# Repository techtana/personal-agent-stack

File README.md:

# personal-agent-stack

**Direction (2026-10-26): private first.** Every request is to be processed by private models, on owned hardware
or confidential cloud VMs; external model APIs become an optional, explicit, gated user choice. The plans are in
[docs/plans/](docs/plans/README.md). Since 2026-10-26 the build routes every tier to local models, with or without an
API key; external models stay off until the privacy gate exists.

A local-first coding-agent stack for one developer on one GPU workstation, composed from open-source
tools rather than a custom harness. Six department agents (app-dev, testing, security, devops,
code-review, docs) are defined once and generated into Claude Code, OpenCode, Open WebUI and a LiteLLM
gateway that routes each request to the cheapest tier that can do the job: a small always-resident
model for autocomplete, a mixture-of-experts coder on the local GPU for routine work, and Claude
Haiku/Sonnet/Opus 5.5 through the gateway only when complexity, context size or a stall demands it.

```
 Claude Code (terminal / VS Code / desktop)   OpenCode   Open WebUI (chat, thumbs)   promptfoo (evals)
            │ Anthropic /v1/messages              │ OpenAI /v1       │                     │
            └──────────────┬──────────────────────┴──────────────────┴─────────────────────┘
                           ▼
            LiteLLM gateway :4000  (one model alias per department = complexity router)
              local-fim · local-small · local-primary   (private only; external models off: policy/privacy.yaml)
              JSONL traces → traces/litellm/     OTLP → Phoenix :6006
                 │                                              │
      Ollama (native, GPU) :11434
      qwen2.5-coder:1.5b-base · qwen3.5:9b · qwen3.6:35b-a3b-coding (MoE, experts in RAM)

 Orchestrator MCP :8765  delegate/get_job/record_lesson   ·   hooks → traces/claude/   ·   nightly retro → PR
```

Design, decisions and measurements: [docs/ORCHESTRATOR-DESIGN.md](docs/ORCHESTRATOR-DESIGN.md).
Private-first multi-user plans (cloud-led on confidential VMs, local-led), privacy gate and installation:
[docs/plans/](docs/plans/README.md).
Stable rules for agents: [AGENTS.md](AGENTS.md). State and lessons: [memory/](memory/).
Manuals: [installation](docs/manuals/installation.md) · [choosing drives](docs/manuals/choosing-drives.md) ·
[user guide](docs/manuals/user-guide.md) · [troubleshooting](docs/manuals/troubleshooting.md).

**When to use it:** you write code with AI agents on your own GPU workstation, and you want routine work to stay
local, private and free. External models are off; they will only ever be an explicit, gated choice (docs/plans/).
It is not a team or hosted service yet.

## Prerequisites

| Tool | Version | Notes |
|---|---|---|
| NVIDIA GPU | 12 GB VRAM for the default lineup; 8 GB works with the `small-gpu` class | 32 GB system RAM enables the MoE primary; 16 GB falls back to a dense 9B |
| [uv](https://docs.astral.sh/uv/) | 0.12+ | the only hard requirement; it fetches Python 3.11/3.12 and the tools |
| [Ollama](https://ollama.com/download) | 0.40+ | native install (Windows: `winget install --id Ollama.Ollama`); not in Docker |
| Claude Code | 2.1.293+ | `winget install --id Anthropic.ClaudeCode` or the VS Code extension / desktop app |
| Node | 24+ | only for `npx promptfoo` evals |

Docker is optional (`infrastructure/docker-compose.yml`); the reference machine runs everything natively.

## Quick start

```powershell
# Windows: double-click install.cmd (or run .\scripts\setup.ps1). It installs the app into its own folder
# (%LOCALAPPDATA%\Programs\AgentStack; its logs, settings and data stay there, not in this repository). Then a
# window asks which features to install (each row shows its disk, GPU, CPU and RAM load on this PC; the local
# models and the gateway are required) and where the models and the Python tools go, and setup runs in the
# background: .env secrets, Ollama env, uv tools, configs, model downloads. Run install.cmd again after a pull
# to update the app, or Install / Remove on the tray's Features card to add or remove features.
uv run scripts/stack.py up   # start phoenix, litellm, orchestrator, open_webui
uv run scripts/stack.py smoke
```

```bash
# Linux / macOS / WSL / Git Bash
./scripts/setup.sh && uv run scripts/stack.py up && uv run scripts/stack.py smoke
```

To keep the stack running in the background, use the tray app instead of `up`:

```
uv run scripts/stack.py tray                    # starts the services and a tray icon (Windows: under the ^ hidden icons)
uv run scripts/stack.py tray --install-startup  # optional: start the tray at login
```

Clicking the icon opens a status window with three tabs (since 2026-10-27): **Overview** (services, start/stop, models
loaded in Ollama), **Usage** (requests, tokens, latency, tok/s and cost per model, from `traces/litellm/`) and
**Settings** (models, context sizes, tracing, Open WebUI, Ollama runtime; **Apply** saves to `machines/<HOST>.yaml`,
rebuilds and restarts what changed) and **Resources** (live CPU, RAM,
driver-reported GPU engine use and dedicated GPU memory per process; unavailable readings show as `-`). The icon is green when everything is up, amber when something is down, red when
the gateway or Ollama is down. The tray runs outside any terminal or Claude Code session, so its services keep running.
"Quit (keep services running)" closes only the tray; "Stop services and quit" stops everything.

After a quit, start it again from the Start menu entry **Agent Stack** (the installer creates it) or by double-clicking
`start.cmd` in the repository folder; either opens the window when the tray is already running. `stop.cmd` closes the
tray and stops its services (Ollama keeps running), even when the tray has already been quit.

For services that must run before anyone signs in (edge mode), register one Task Scheduler task per service instead,
from an elevated terminal: `uv run scripts/stack.py tasks install`. See the
[installation manual](docs/manuals/installation.md#run-the-services-before-sign-in-optional).

Then:

- **Claude Code on your subscription (default):** open this repo in Claude Code. The departments appear as
  subagents (`@security review src/auth.py`), `/retro`, `/harden`, `/brainstorm`, `/why-routed` as skills,
  `/ux-rules` for UX reviews against a researched rule catalog, `/claude-security-audit` for a privacy and safety
  check of your Claude setup, and the orchestrator as an MCP server (approve it once). Heavy work stays on your plan.
- **Claude Code on the local gateway:** `.\scripts\claude-local.ps1` (or `.sh`). A separate config dir
  (`~/.claude-local`) points at LiteLLM, so local models serve `sonnet`/`haiku` aliases and plan quota is untouched.
- **Open WebUI:** http://127.0.0.1:3000 -> create the admin user -> Workspace -> Models -> Import each
  `config/openwebui/<dept>.json`; Admin -> Integrations -> External Tool Servers -> MCP (Streamable HTTP)
  `http://127.0.0.1:8765/mcp` with `ORCHESTRATOR_BEARER` from `.env` as the bearer (not `WEBUI_SECRET_KEY`) and
  ID `personal-agent-stack`; the department models switch its tools on in new chats.
- **OpenCode:** `opencode.json` registers the gateway as provider `litellm`; agents are in `.opencode/agents/`.
- **Autocomplete in VS Code:** `config/continue/config.yaml` (Continue, autocomplete role only).

## Configuration

| Where | What |
|---|---|
| `machines/_defaults.yaml` | hardware classes -> model lineup, Ollama env, ports, service modes |
| `machines/<HOST>.yaml` | detected hardware + your overrides (`models.primary`, `model_store`); written by the installer, local to this computer, never committed |
| `policy/privacy.yaml` | private-first policy: deployment location, `external.enabled` (off; the build refuses `true` until the privacy gate exists) |
| `agents/<id>.yaml` | one department: prompt, tools, Claude Code model alias, routing tiers, evals |
| `agents/_common.md` | working agreements appended to every department prompt |
| `.env` | `LITELLM_MASTER_KEY`, `ORCHESTRATOR_BEARER`, `WEBUI_SECRET_KEY`, Claude Code's own `LITELLM_CLAUDE_KEY` and `ORCHESTRATOR_CLAUDE_BEARER`, `ANTHROPIC_API_KEY` (unused until external models exist) |
| `.claude/settings.json` | hooks (trace capture), permissions, gateway hint headers |
| `.claude/settings.local.json` | per-machine: Claude Code's own keys (never the stack's), `autoMemoryDirectory` -> `memory/claude/` |

After any change: `uv run scripts/stack.py build` (and `up`/`down` to restart the gateway).

## Cost model

- Autocomplete, embeddings, titles/summaries and the simple/medium tiers are local: $0.
- Every tier is local, with or without an API key in `.env` (private first, since 2026-10-26). External models will be
  explicit aliases behind the privacy gate, never a tier or fallback (docs/plans/SHARED-COMPONENTS.md section 2).
- Interactive Claude Code on the subscription costs no API dollars; a credential variable (profile B or
  an API key in the gateway) bills per token. Traces record cost per request; `retro` reports cost per department.

## Commands

```
uv run scripts/stack.py doctor [--write-profile [--refresh]]   hardware, tools, ports, chosen class
uv run scripts/stack.py check [--no-drives] [--json]          this PC, and which models and features are recommended on it
uv run scripts/stack.py profile | build | setup | pull [--all]
uv run scripts/stack.py up [svc...] | down [svc...] | status
uv run scripts/stack.py tray [--show | --foreground | --status | --stop | --install-startup | --remove-startup]
uv run scripts/stack.py tasks install|remove|start|stop|status|xml [svc...] [--trigger startup|logon]
uv run scripts/stack.py bench [--model m] [--num-ctx n] [--tokens n] [--runs n]
uv run scripts/stack.py smoke [--dept id] [--skip-mcp] [--media | --media-only]
uv run scripts/stack.py media check|install|provision          ComfyUI and image models under media.root (path guard first)
uv run scripts/stack.py media gpu chat|media                   hand the GPU to chat (free ComfyUI) or media (unload Ollama)
uv run scripts/stack.py dictate install|start|stop|status|check voice typing in any app: Ctrl+Alt+D or the mic button; Ctrl+Alt+R or the pencil button refines selected text
uv run scripts/stack.py dictate transcribe note.wav [--style concise] [--model m]   the voice typing pipeline on a recording
uv run scripts/stack.py why-routed [--last n] [--days n]
uv run scripts/stack.py retro -- --days 7 [--reflect local-small|none] [--pr]
uv run scripts/stack.py skills-sync [--dry-run]                 copy your own skills into skills/ (rules: skills/sync.yaml)
npx promptfoo@0.125.0 eval -c evals/<dept>/promptfooconfig.yaml --repeat 3
```

## Troubleshooting

See [docs/manuals/troubleshooting.md](docs/manuals/troubleshooting.md): health checks, log locations and a
symptom → cause → fix table. Logs are in `.run/logs/<service>.log`; Ollama's is `%LOCALAPPDATA%\Ollama\server.log`.

## Assumptions and limitations

- It is built for one developer on one workstation. Every service listens on 127.0.0.1 only, and nothing is multi-user.
- It needs an NVIDIA GPU with at least 8 GB of VRAM. On 32 GB of RAM, the 35B MoE decodes at about 25 tok/s,
  against about 52 for the dense 9B (the reference machine, 2026-10-25).
- Only Windows is verified (2026-10-26). Service management on Linux and macOS is written but untested, and so is the Docker compose path.
- Cloud tiers have not been exercised yet, because no API key is on the reference machine. Claude Code profile B has
  not been run as a live session yet. Since 2026-10-28 the build is private only, so no tier can reach an external
  model at all (`policy/privacy.yaml`, `external.enabled: false`).
- AI agents on the machine run as the owner's own account, so nothing at the operating-system level stops them reading
  personal files. A plan to fix that exists ([AGENT-FILE-ISOLATION.md](docs/plans/AGENT-FILE-ISOLATION.md)); nothing
  is applied yet.
- Routing budgets and LiteLLM's adaptive router need Postgres, so they are not in use.

## Known issues

Tracker: this repository's GitHub issues.

- Phoenix does not start on the reference machine since 2026-10-26: Smart App Control blocks compiled modules in its tool
  environment (pyarrow, sqlalchemy, pandas). The plans remove Phoenix; until then turn **Phoenix tracing** off in the
  tray's Settings tab. The tray's Usage tab reads the JSONL traces and does not need Phoenix.
- Smart App Control may also start blocking the uv tool environments' `python.exe` (see the open items in `memory/state.md`).
- The LiteLLM admin UI (`/ui`, the tray's **Open gateway admin** link) shows "Not connected to DB!" because it needs Postgres.
- Images (2026-11-04): Smart App Control refused PyAV 19.0.2 and 16.0.1 inside ComfyUI's environment; 17.0.0 runs,
  so setup pins `av==17.0.0` (`media.SAC_PINS`). A future refusal shows as "An Application Control policy has blocked
  this file" in `.run/logs/comfyui.log`.
- Vision, speech, the Auto router, style transfer, video with audio, music and web search from the multimodal plan
  are not built yet (docs/design/plans/2026-11-01-multimodal-stack.md).
- `local-reviewer` points at `flint:40b-a2b`, which is not pulled. No tier routes to it.
- A chat message cannot switch models. Open WebUI sends each message to the model picked in the chat's model list
  (or with `@` in the input box), and `local-primary` is always the local model.
- `/ux-rules` lives in `.claude/skills/ux-rules/`, not in the `skills/` library. The commit that moves it (`a8400c9`)
  landed on the PR branch after PR #13 merged (2026-11-01).
- D: on the reference machine is exFAT, which has no file permissions, so any account can read everything on it (found
  2026-10-30). Personal data there must move, or the drive must be reformatted to NTFS, before the agent account split
  can protect it.
- From 2026-10-26 (`d93211b`) to 2026-11-07 a stray Open WebUI database (`litellm.db`, `-shm`, `-wal`) was committed at
  the repository root. Its user and chat tables were empty, but its settings held the gateway's `LITELLM_MASTER_KEY`,
  and it is still in the public history. Rotate that key.
- Until 2026-11-07 the machine profile, docs and three commits' author field named the owner's computer, Windows
  account or email address. The current files no longer do; the git history and the pull request pages on GitHub
  still do.
- The Claude Code hook log (`scripts/hooks/log_turn.py`, `traces/claude/`) keeps the first 200 characters of the last
  assistant message and the first 300 characters of each Bash command, although its docstring says no prompt or file
  contents are stored (found 2026-11-01).

## Path forward

Running list. Add new items; don't rewrite old ones.

- 2026-10-27: elevated steps from B-S0/B2b: `winget configure --enable`, then `stack.py tasks install --trigger startup`
  once B2 lands.
- 2026-10-27: apply `winget/configuration.winget` on a clean Windows account (B3).
- 2026-10-27: remove Phoenix from the stack (plan item R); it no longer starts on the reference machine.
- 2026-10-26: tray app design, plus CPU, RAM and GPU use per process (#4). Design and usage done 2026-10-27 (PR #9);
  the per-process view (Resources tab) landed with PR #8.
- 2026-10-25: confirm that the tray and its services start on their own after a reboot.
- 2026-10-25: Open WebUI first run (admin user, model import, MCP server).
- 2026-10-25: add `ANTHROPIC_API_KEY` and verify the cloud tiers. (Superseded 2026-10-26: private first, no cloud tiers.)
- 2026-10-25: run `scripts/claude-local.ps1` end to end on the 9B at 32k.
- 2026-10-25: try the 35B as primary again after a RAM upgrade; try tuning `LLAMA_ARG_N_CPU_MOE`.
- 2026-10-25: first `/retro` after a week of real traces; wire up the Open WebUI thumbs export.
- 2026-10-25: test service management on Linux and macOS.
- 2026-10-26: build is private only (S6/B1 core): no automatic cloud tiers. Next: privacy gate S1/S2, guardrail S3,
  evals S8, then B2 services, R removals and the `stack.py install` installer (B3). Merged to `main` 2026-10-28 (PR #8).
- 2026-10-31: create the weekly `skills-sync` scheduled task from `skills/sync-task-prompt.md` and click **Run now** once.
- 2026-11-01: hard block on AI agents reading personal files: decide D1-D4, deal with the exFAT D: drive, finish the
  V-F checks, then build `stack.py isolate` (I2) ([plan](docs/plans/AGENT-FILE-ISOLATION.md)).
- 2026-11-01: merge `a8400c9` to move `/ux-rules` into `skills/`; run the second `ux-rules` eval round with the
  sharper assertions.
- 2026-11-01: remove the stray `litellm.db*` files from the repository root and ignore them. Done 2026-11-07.
- 2026-11-01: multimodal stack (vision, speech, images, style transfer, video with audio, music, web search, routing
  per message): plan proposed, nothing built. Start from [docs/HANDOFF-2026-11-01-multimodal.md](docs/HANDOFF-2026-11-01-multimodal.md).
- 2026-11-07: rotate `LITELLM_MASTER_KEY` (it was in the committed `litellm.db`): `.env`, Open WebUI's gateway
  connection and `~/.openclaw/.env`, then restart the tray.
- 2026-11-07: decide whether to rewrite git history so past commits no longer carry the computer name, the account
  name, the database or a personal email address; GitHub keeps pull request pages until GitHub Support purges them.

## Design decisions

Running log of the most important decisions. Never delete an entry; mark a reversed one as superseded. The full log,
with reasons and rejected alternatives, is [docs/design/DECISIONS.md](docs/design/DECISIONS.md); plans and their status
are indexed in [docs/design/](docs/design/README.md).

- 2026-10-24: Compose existing tools (Claude Code, OpenCode, LiteLLM) instead of building a custom harness. A
  hand-rolled proxy broke tool-using clients.
- 2026-10-24: Run Ollama and every service natively, with no Docker or WSL2, which would reserve RAM the MoE needs.
- 2026-10-24: Ollama is the only local inference engine, because it already runs llama-server with MoE-aware placement.
- 2026-10-24: Define each department once in `agents/*.yaml` and generate every tool's files from it. Duplicated prompts drifted.
- 2026-10-24: Self-improvement is a human-gated PR loop with an eval gate. Nothing merges automatically.
- 2026-10-24: Name the orchestrator secret `ORCHESTRATOR_BEARER`, because Claude Code blanks `*_TOKEN` and `*_API_KEY` in `.mcp.json`.
- 2026-10-25: Make the reference machine's primary `qwen3.5:9b` at 32k instead of the 35B MoE: twice the decode speed and
  about 17 GB of RAM left free.
- 2026-10-25: Local tiers that share a model use the same `num_ctx` and load options, so Ollama never reloads between them.
- 2026-10-25: Start uv tools through their environment's `python.exe`, because Smart App Control blocked the `~/.local/bin` launchers.
- 2026-10-25: Identify a service by pid plus process start time, because Windows reuses pids.
- 2026-10-25: Starting services with `CREATE_BREAKAWAY_FROM_JOB` from an agent shell (superseded the same day; it
  was unreliable). The tray app launched through Explorer now owns the services.
- 2026-10-26: Private first. External model APIs are off at install and become an explicit, gated user choice. This
  supersedes automatic cloud tiers.
- 2026-10-26: Build the privacy plans on existing open-source tools (Presidio, detect-secrets, deface, ExifTool,
  Keycloak/Authentik) and write only glue.
- 2026-10-26: Edge mode runs each service under a Task Scheduler task with a 2-minute watchdog trigger, because Task
  Scheduler's restart on failure does not restart a killed process.
- 2026-10-26: Windows dependencies come from a generated winget configuration file, so the install is unattended and reviewable.
- 2026-10-27: The tray's Settings tab edits `machines/<HOST>.yaml` and restarts only what changed; cloud tiers stay
  read-only there, because turning them on is a deliberate `.env` decision.
- 2026-10-28: The private-only build is on `main` (PR #8): a tier, fallback, default or profile B alias that names an
  external model fails the build.
- 2026-10-29: Proposed, not decided: block AI agents from personal files with a separate standard Windows account and
  NTFS deny entries, because every agent's own settings are advisory on native Windows.
- 2026-10-31: Version the owner's own skills in `skills/` with a one-way `skills-sync`; never sync Anthropic's,
  proprietary or personal-data skills, because the repository is public.
- 2026-11-01: UX reviews use `/ux-rules`, a catalog of 122 researched rules with evidence grades; it will not help
  A/B-test deceptive patterns.
- 2026-11-07: Machine profiles are local: the installer writes `machines/<HOST>.yaml` and git ignores it, because the
  repository is public and the profile names the computer. Docs say "the reference machine" and "the owner"; a test
  fails when this machine's own names reach a tracked file.

## Background knowledge

The stack rests on a few domains a newcomer may not know: how local models use GPU memory, how a gateway routes
requests, how privacy is enforced rather than advised, how Windows keeps background services alive, and how coding
agents improve from traces. Start with [docs/knowledge/README.md](docs/knowledge/README.md), which gives a reading
order and a glossary.

## Repository layout

```
agents/            department source of truth (+ _common.md)        machines/   hardware profiles
scripts/           stack.py CLI, stacklib/, tray.py, retro.py, hooks/   orchestrator/  FastMCP server + job store
winget/            configuration.winget, configuration.edge.winget (generated by `stack.py build`)
infrastructure/    litellm/ (config.yaml generated, custom_callbacks.py), docker-compose.yml (optional)
.claude/           settings, skills (retro, harden, brainstorm, why-routed, ux-rules, claude-security-audit), agents/ (generated)
skills/            your own skills library, synced weekly by a scheduled task (README, sync.yaml, sync-task-prompt.md)
.opencode/ opencode.json  config/openwebui/ config/continue/   evals/ (generated gates)   memory/   traces/   retro/
docs/              ORCHESTRATOR-DESIGN.md, manuals/, plans/ (private-first plans), design/ (decision log, plan index),
                   knowledge/ (domain background for newcomers), decisions/ (ADRs), research/, archive/,
                   HANDOFF-2026-10-24.md
```

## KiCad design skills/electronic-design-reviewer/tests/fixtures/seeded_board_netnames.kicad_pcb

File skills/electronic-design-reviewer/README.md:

# electronic-design-reviewer toolkit

Optional companion files for the **electronic-design-reviewer** skill. The skill works without
them (its SKILL.md is self-contained); with them, reviews are faster and the numbers are
computed by tested code instead of ad-hoc arithmetic.

## Where to put it

The skill looks for this folder (named `electronic-design-reviewer-toolkit` or containing
`scripts/netlist_lint.py`) in this order:
1. next to SKILL.md (a local skill folder, e.g. `~/.claude/skills/electronic-design-reviewer/`);
2. among the conversation's files: attached, Project files, a linked folder on your computer,
   or a repository;
3. not found → the skill uses its inline procedures.

## Contents

| Path | What it is |
|---|---|
| `scripts/netlist_lint.py` | Schematic checks on a KiCad netlist (.net/.xml), a .kicad_pcb, or a CSV pin list. Each hit maps to a guide rule ID. |
| `scripts/pcb_check.py` | Layout checks on a .kicad_pcb: plane assignment, Inner1 traces, one via per ground pad, decap distance, fiducials, markers, vias, paste, copper balance, IR drop. |
| `scripts/ee_calc.py` | 19 calculators (RC, MLCC DC bias, SRF, PDN impedance, divider, resistor power, Tj, LDO, trace R/width, via, annular ring, microstrip, I2C pull-up, crystal caps, battery life, flyback, hot-plug, pulse sag). |
| `scripts/compliance_score.py` | Assessment template, weighted guide compliance, coverage and verdict gate. |
| `references/guide-rosenberg-v5.md` | Full rule pack (95 rules) with why/teach notes and page references. |
| `references/expert-checks.md` | ~60 senior-engineer checks beyond the guide (power, battery, MCU, analog, RF, drivers, safety/EMC, DFM, test, supply chain). |
| `references/verification-playbook.md` | Connector discovery, SpiceBridge recipes R1-R10, KiCad commands, fallbacks, verification log. |
| `references/evidence-and-research.md` | Evidence tags, source tiers, conflict resolution, datasheet checklist. |
| `references/teaching-style.md` | The mentor voice: Finding Card examples, analogy bank, depth calibration. |
| `references/report-template.md` | Report structure and the assessment JSON format. |
| `references/learning-loop.md` | Feedback events, escape analysis, promotion rules, storage. |
| `references/guide-ingestion.md` | Turning any new guide or company standard into a rule pack. |
| `assets/sim/*.cir` | ngspice netlists for the SpiceBridge recipes (flyback, MLCC timing, PDN, LC filter, part stress, tolerance, hot-plug, coin-cell sag, op-amp stability). |
| `assets/ledger-template.md` | Per-project review ledger (facts, waivers, findings, escapes, learner profile). |
| `evals/` | Three test cases with graders (seeded-fault netlist, MLCC timing decision, relay escape). |
| `tests/test_toolkit.py` | 19 regression tests for the scripts (run `python3 tests/test_toolkit.py`). |

All scripts are Python 3.8+ standard library only. Every script prints `-h` help.

## Quick start

```
python3 scripts/netlist_lint.py my_board.net --sch my_board.kicad_sch
python3 scripts/pcb_check.py my_board.kicad_pcb
python3 scripts/ee_calc.py mlcc --c 10u --vrated 6.3 --vbias 5 --dielectric X5R --size 0603
python3 scripts/compliance_score.py --rules references/guide-rosenberg-v5.md --stage schematic --template > assessment.json
```

Script output is a list of **leads**, not verdicts: the reviewer confirms each one before
reporting it. `pcb_check.py` geometry is approximate (beta).

The rule pack paraphrases *The Electronic Product Development Checklist* v5 by Hans Rosenberg
(hans-rosenberg.com), supplied by the user. Refer to the original for exact wording.

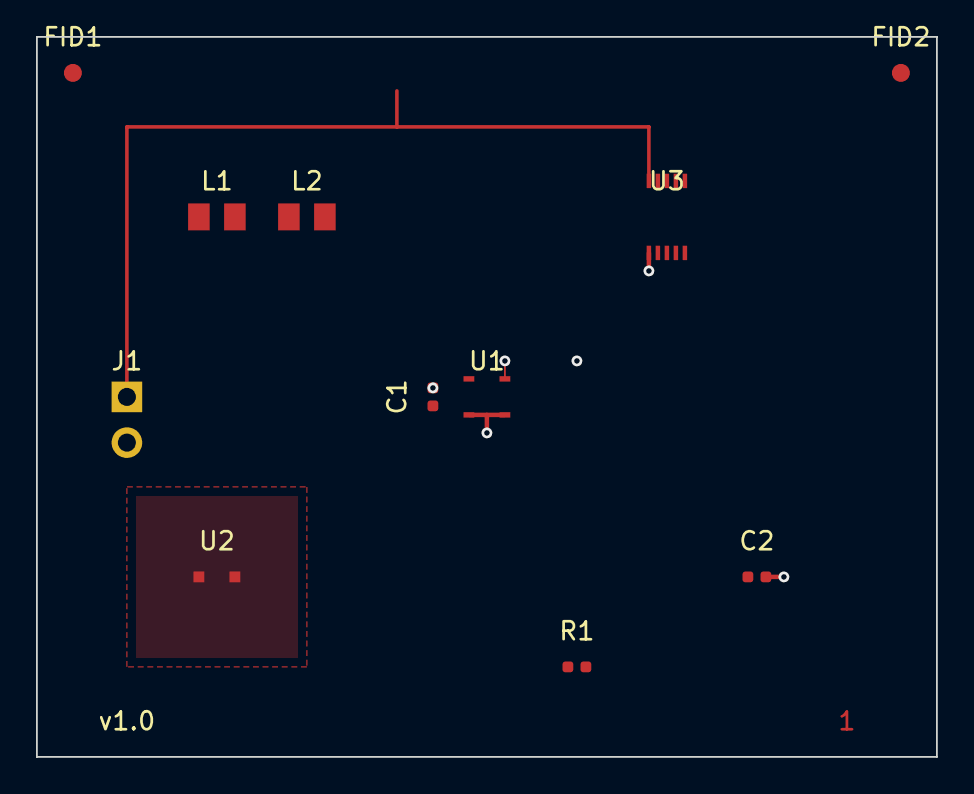
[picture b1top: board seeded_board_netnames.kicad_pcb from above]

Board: 4 copper layers, 50.0 x 40.0 mm, 11 parts (0 on the bottom side), 4 nets.

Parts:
C1, C2: 100n; C_0402_1005Metric
FID1, FID2: Fiducial; Fiducial_1mm_Mask2mm
J1: PWR; PinHeader_1x02
L1, L2: 10u; L_1210_test
R1: 4k7; R_0402_1005Metric
U1: MCU; QFN-4_test
U2: SENSOR; SOT-23_test
U3: FINEPITCH; TSSOP-10_test

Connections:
+3V3: C1.1, C2.1, U1.1 (VDD), U2.1 (VDD)
GND: C1.2, C2.2, J1.2, R1.2, U1.2 (GND), U1.3 (GND), U2.2 (GND), U3.6
SDA: R1.1, U1.4 (SDA)
VBUS: J1.1, U3.1

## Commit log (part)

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2026-06-07 feat: add complete local coding agent stack
    Six specialized agents (app-developer, testing, security, devops,
    code-review, docs) with automatic local/cloud routing. Simple tasks
    run on local Ollama models; complex requests escalate to Claude API
    based on token count and keyword classification.
    Includes: Docker Compose stack, FastAPI OpenAI-compatible router,
    Ollama Modelfiles, VS Code Continue config, and setup scripts.
